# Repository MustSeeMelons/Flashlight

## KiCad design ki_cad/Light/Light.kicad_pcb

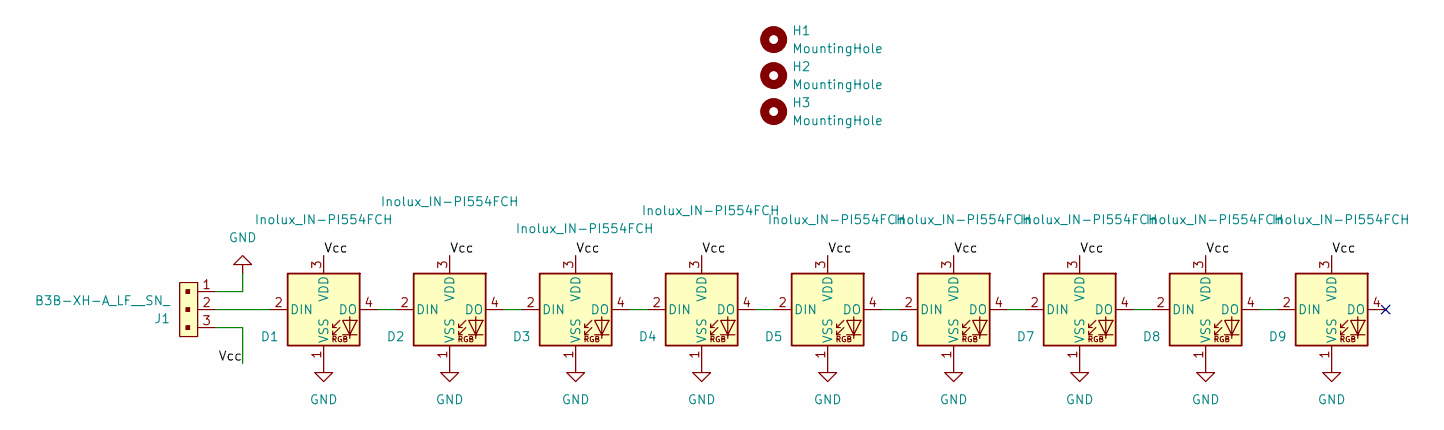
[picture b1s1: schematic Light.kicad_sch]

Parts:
D1, D2, D3, D4, D5, D6, D7, D8, D9: Inolux_IN-PI554FCH; LED_Inolux_IN-PI554FCH_PLCC4_5.0x5.0mm_P3.2mm
H1, H2, H3: MountingHole; MountingHole_2.1mm
J1: B3B-XH-A_LF__SN_; PinHeader_1x3_P2.5mm_Drill1.1mm; MPN B3B-XH-A(LF)(SN); Digi-Key_PN 455-2248-ND

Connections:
/Vcc: D1.3 (VDD), D2.3 (VDD), D3.3 (VDD), D4.3 (VDD), D5.3 (VDD), D6.3 (VDD), D7.3 (VDD), D8.3 (VDD), D9.3 (VDD), J1.3
GND: D1.1 (VSS), D2.1 (VSS), D3.1 (VSS), D4.1 (VSS), D5.1 (VSS), D6.1 (VSS), D7.1 (VSS), D8.1 (VSS), D9.1 (VSS), J1.1
unnamed: D1.2 (DIN), J1.2
unnamed: D1.4 (DO), D2.2 (DIN)
unnamed: D2.4 (DO), D3.2 (DIN)
unnamed: D3.4 (DO), D4.2 (DIN)
unnamed: D4.4 (DO), D5.2 (DIN)
unnamed: D5.4 (DO), D6.2 (DIN)
unnamed: D6.4 (DO), D7.2 (DIN)
unnamed: D7.4 (DO), D8.2 (DIN)
unnamed: D8.4 (DO), D9.2 (DIN)

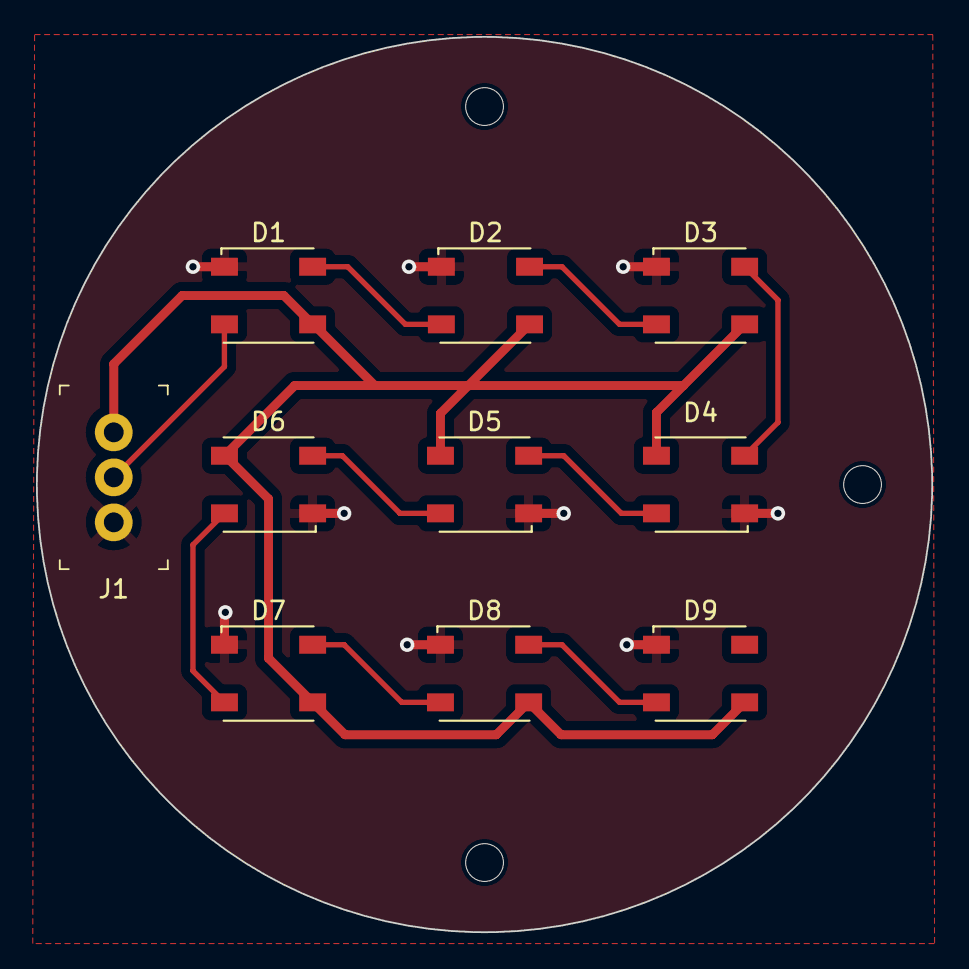
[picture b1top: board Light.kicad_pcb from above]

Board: 2 copper layers, 49.7 x 49.7 mm, 13 parts (0 on the bottom side), 11 nets.

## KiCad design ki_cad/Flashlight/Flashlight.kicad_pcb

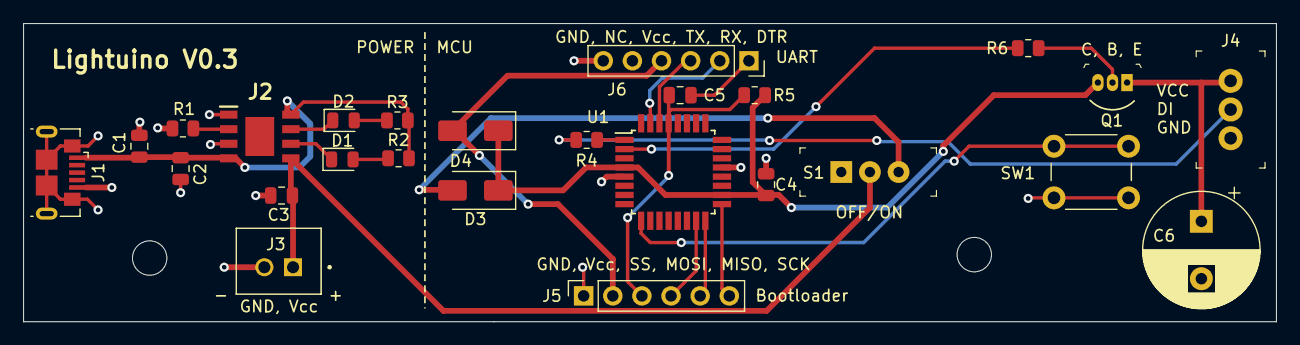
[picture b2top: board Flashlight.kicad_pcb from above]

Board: 2 copper layers, 109.2 x 26.0 mm, 28 parts (0 on the bottom side), 24 nets.

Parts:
C1, C4, C5: 100 nF; C_0805_2012Metric
C2, C3: 10 uF; C_0805_2012Metric
C6: 220 uF; CP_Radial_D10.0mm_P5.00mm
D1, D2: LED; LED_0805_2012Metric
D3, D4: B120-E3; D_SMA
H1, H2: MountingHole; MountingHole_3mm
J1: USB3080-XX-01-A_REVE; USB_Micro-B_GCT_USB3076-30-A
J2: TP4056; SOIC127P600X175-9N
J3: B2B-XH-A(LF)(SN); JST_B2B-XH-A(LF)(SN)
J4: B3B-XH-A_LF__SN_; PinHeader_1x3_P2.5mm_Drill1.1mm
J5, J6: Conn_01x06_Socket; PinSocket_1x06_P2.54mm_Vertical
Q1: 2N3904BU; TO-92-3
R1: 5K; R_0805_2012Metric
R2, R3: 1K; R_0805_2012Metric
R4, R6: 330R; R_0805_2012Metric
R5: 10K; R_0805_2012Metric
S1: EG1218; Switch_Slide_11.6x4mm_EG1218
SW1: SW_Push_Open; SW_PUSH_6mm
U1: ATmega328PB-A; TQFP-32_7x7mm_P0.8mm

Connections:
/BAT+: D3.2 (A), S1.3
/CHARGE: D2.1 (K), J2.7 (~CHRG)
/DI_PIN: J4.2, R4.2
/DTR: C5.1, J6.1
/MISO_PB4: J5.5, U1.16 (PB4)
/MOSI_PB3: J5.4, U1.15 (PB3)
/PROG_SS: C5.2, J5.3, R5.1, U1.29 (~RESET/PC6)
/PWR: C4.1, D3.1 (K), D4.1 (K), Q1.3 (C), R5.2, U1.4 (VCC), U1.18 (AVCC)
/RX: J6.3, U1.30 (PD0)
/SCK_PB5: J5.6, U1.17 (PB5)
/STANDBY: D1.1 (K), J2.6 (~STDBY)
/STRIP_VCC: C6.1, J4.3, Q1.1 (E)
/TX: J6.2, U1.31 (PD1)
/UART_Bus: D4.2 (A), J5.2, J6.4
/VBUS: C1.1, C2.1, J1.1 (VBUS), J2.4 (VCC4), J2.8 (CE), R2.1, R3.1
GND: C1.2, C2.2, C3.2, C4.2, C6.2, J1.5 (GND), J2.1 (TEMP1), J2.3 (GND_3), J3.2, J4.1, J5.1, J6.6, R1.2, SW1.2 (B), U1.5 (GND), U1.21 (GND)
unnamed: D1.2 (A), R2.2
unnamed: D2.2 (A), R3.2
unnamed: C3.1, J2.5 (BAT), J3.1, S1.2
unnamed: J2.2 (PROG2), R1.1
unnamed: Q1.2 (B), R6.2
unnamed: SW1.1 (A), U1.9 (PD5)
unnamed: R4.1, U1.1 (PD3)
unnamed: R6.1, U1.2 (PD4)

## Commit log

2023-11-13 Hello there
2023-11-15 Add STLs
